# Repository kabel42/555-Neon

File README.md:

A simple 555 based circuit to drive NE-2 neon lamps from 5V USB.
The aim of the Project was to build something without a microcontroller or software and only using jlcpcb basic parts.

Warning: Might generate Voltages exceeding [ELV](https://en.wikipedia.org/wiki/Extra-low_voltage)

Simulation:
[555 PWM Generator](https://www.falstad.com/circuit/circuitjs.html?ctz=CQAgjCCsB0AM8MUgLAUwLQA4QHY5lkmTACYBmZANksx00pEoE5xYo3IMwwAoMSyCBIlk4ZKJI4SY0bOhMFTIpBWZYZIkx4B3cE2ki2wicjawdeg6ctCpIc7rD7bBkS-s8AxjbKZRT6WQyQKFoTnQCUPEcalhuDSY-ZEFYODiPAHMbIOkAkHFsMx4AExANaXKy2FFK6WLUADMAQwBXABsAFwta2GxKyvMAJSFMbG4DUZA1exnrFJnUyB4AeTLIA178-iFNoqzgtjJqspJD04WLEknxtdzSD11Km6eYjzAcGuPiBkkKmnBWIh7GEQINUABnACW4I6TQAdp5UCUqrJtpVvkIQPVmu0uo91lsGP0CQ53L5-M5yQ8fH4bL8PAB7fKYtimBSsYEIMhMWCUEjzEJkHhMljSQ40D4c1KIJgxSB8wQQXhAA)
[Booster](https://www.falstad.com/circuit/circuitjs.html?ctz=CQAgjOCmC0AcIGZYCYB0B2AbMgrCsALAgJzEAMmBIOZ11tOMYYAUAEogEHxJUFiZEsKrWTgyEiXRwhaZVDhYBzTsUEEpBNZwGzZLADaduiMn20Ize+ZJk2K6bl0vlkJWI-0J0tBJh5WXAFUCNYsAPKqgn7wOFiI-uD6HJYhVsgapiJ6mXbWCiwAZsY8wlFCIWJgCrKoZMgsACblqdRcWSBVAHL83CwAxiDYaVTDnJrgdZLTMxJgMOggxKiY6ISwZAiWq8RaxLVz+ipjGrQnunIRQ7DBIOh+HRBkLADuLYla0VbPbzjtrWNWs9BjEOqCEDgxCIpocCBgbghkJsaMRHMh0GJ7E9UKwVODIQkeIlLmAPNdbv54Kc9GBJOJZlIfAcyKw3icpJTxpc2RkOpygSwAE5gqzg77iFgAe0QiDEoQ0pE6cjqeVY0tp4l5tAV8A2tQgBpYQA)

[BOM](https://kabel42.github.io/555-Neon/)

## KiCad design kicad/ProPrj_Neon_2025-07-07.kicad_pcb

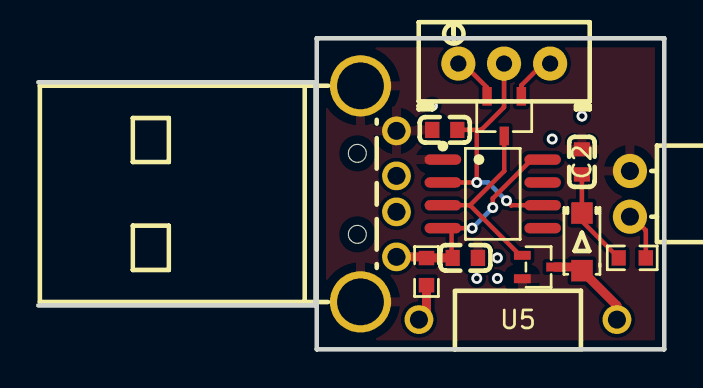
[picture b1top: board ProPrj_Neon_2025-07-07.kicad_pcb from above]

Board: 2 copper layers, 34.8 x 17.3 mm, 13 parts (0 on the bottom side), 10 nets.

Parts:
C1, C2, C3: 100nF; C0603
D2: SOD4007-MS; SOD-123FL_L2.8-W1.8-LS3.7-RD
Q1: BSS123; SOT-323-3_L2.0-W1.3-P1.30-LS2.3-BR
R3: 10K; R0603
R4: 100kΩ; RES-ADJ-TH_3P-L9.5-W4.9-P2.50-L_3296W
R5: 1Ω; R0603
U2: NE555-TD; SOIC-8_L4.9-W3.9-P1.27-LS6.0-BL
U3: HDR-TH_2P-P2.54-H-F-W10.0-N
U4: BAV99; SOT-23-3_L3.0-W1.7-P0.95-LS2.9-BR
U5: 47uH; IND-TH_BD3.2-L7.0-P11.00-D0.5
USB1: USB-AM-TH_AM90

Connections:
/OUT: Q1.1 (G), U2.3 (Output), U4.3 (C)
/TRIG: C1.2, R4.2, U2.2 (Trig), U2.6 (Thres)
<NO NET>: C3.1, R5.2, U2.4 (Reset), U2.8 (VCC), USB1.1 (VCC)
GND: C1.1, C2.2, C3.2, Q1.2 (S), U2.1 (GND), U3.2, USB1.4 (GND), USB1.MH1, USB1.MH2
unnamed: D2.2 (A), Q1.3 (D), U5.2
unnamed: C2.1, D2.1 (K), R3.1
unnamed: R3.2, U3.1
unnamed: R4.1, U4.2 (A)
unnamed: R4.3, U4.1 (A)
unnamed: R5.1, U5.1

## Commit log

2025-07-10 init
2025-07-10 unzip schematic
2025-07-11 fix pcb import, html bom
2025-07-11 try github pages
2025-07-11 add kicad/sym-lib-table
2025-07-11 fix pcb symbols
